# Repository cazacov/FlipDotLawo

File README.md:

# FlipDot34

Controller for the flip-dot display with 34-pin connector. For example produced by Lawo-Luminator-Europa Mark IV Industries GmbH.

Version 28x19

Version 28x24 with LED lights

## Connector Pinout
| Pin |  Function | Pin |  Function |
| --- | ------ | --- | ------ |
| 1   | GND  | 2   | GND  | 
| 3   | GND  | 4   | GND  | 
| 5   | 5V  |  6   | 5V  | 
| 7   | A0-X | 8 | DATA-X |
| 9   | A1-X | 10 | ENABLE-Y-SET |
| 11   | A2-X | 12 | ENABLE-Y-RESET |e
| 13   | B0-X | 14 | ENABLE-X-1 |
| 15   | B1-X | 16 | ENABLE-X-2 |
| 17   | A0-Y | 18 | ENABLE-X-3 |
| 19   | A1-Y | 20 | ENABLE-X-4 |
| 21   | A2-Y | 22 | ENABLE-X-5 |
| 23   | B0-Y | 24 | ENABLE-X-6 |
| 25   | B1-Y | 26 | ENABLE-X-7 |
| 27   | n/c | 28 | ENABLE-X-8 |
| 29   | 24V  |  30   | 24V  | 
| 31   | GND  | 32   | GND  | 
| 33   | GND  | 34   | GND  | 

## Chaining Multiple Displays in a Row

Driver board has two connectors. The output connector ST2 mostly duplicates 1:1 singnals from the input ST1 but ENABLE-X- signals are shifted. 

| Pin | INPUT  ST1 |  OUTPUT ST2 |
| --- | ---------- | ---------- |
| 13  | ENABLE-X-1 | ENABLE-X-2 |
| 15  | ENABLE-X-2 | ENABLE-X-3 |
| 17  | ENABLE-X-3 | ENABLE-X-4 |
| 19  | ENABLE-X-4 | ENABLE-X-5 |
| 21  | ENABLE-X-5 | ENABLE-X-6 |
| 23  | ENABLE-X-6 | ENABLE-X-7 |
| 25  | ENABLE-X-7 | ENABLE-X-8 |
| 17  | ENABLE-X-8 | ENABLE-X-1 |

The ENABLE input of FP2800 X Driver is always connected to ENABLE-X-1 connector pin. For example when ENABLE-X-3 is set to HIGH the first two displays in a row will ignore it, but after two decrements the signal will be applied to ENABLE-X-1 ST1 of the third display matrix and will activate it.

## Driver Boards

### Prototype

This prototype uses Arduino Nano and two 74HC595 shift registers to control up to 6 matrices. By adding another 595 it can control up to 8 display matrices.

### FlipDot34Nano

Driver board with Arduino Nano and three 74HC595 shift registers opitmized for single-sided PCB that can be milled with 3018 CNC. 3 digital pins are used for controlling shift registers, analog pins A4 and A5 can be used to receive commands over I2C. Pins A0-A2 connected to DIP switches choosing I2C address.

Schematic in KiCad 6 format checked in under .\Driver-boards\FlipDot34Nano\schematic\FlipDot34Nano

---
All trademarks, logos and brand names are the property of their respective owners. All company, product and service names are for identification purposes only. 

It's a hobby project; I am not affiliated with any  company producing flip-dot displays.

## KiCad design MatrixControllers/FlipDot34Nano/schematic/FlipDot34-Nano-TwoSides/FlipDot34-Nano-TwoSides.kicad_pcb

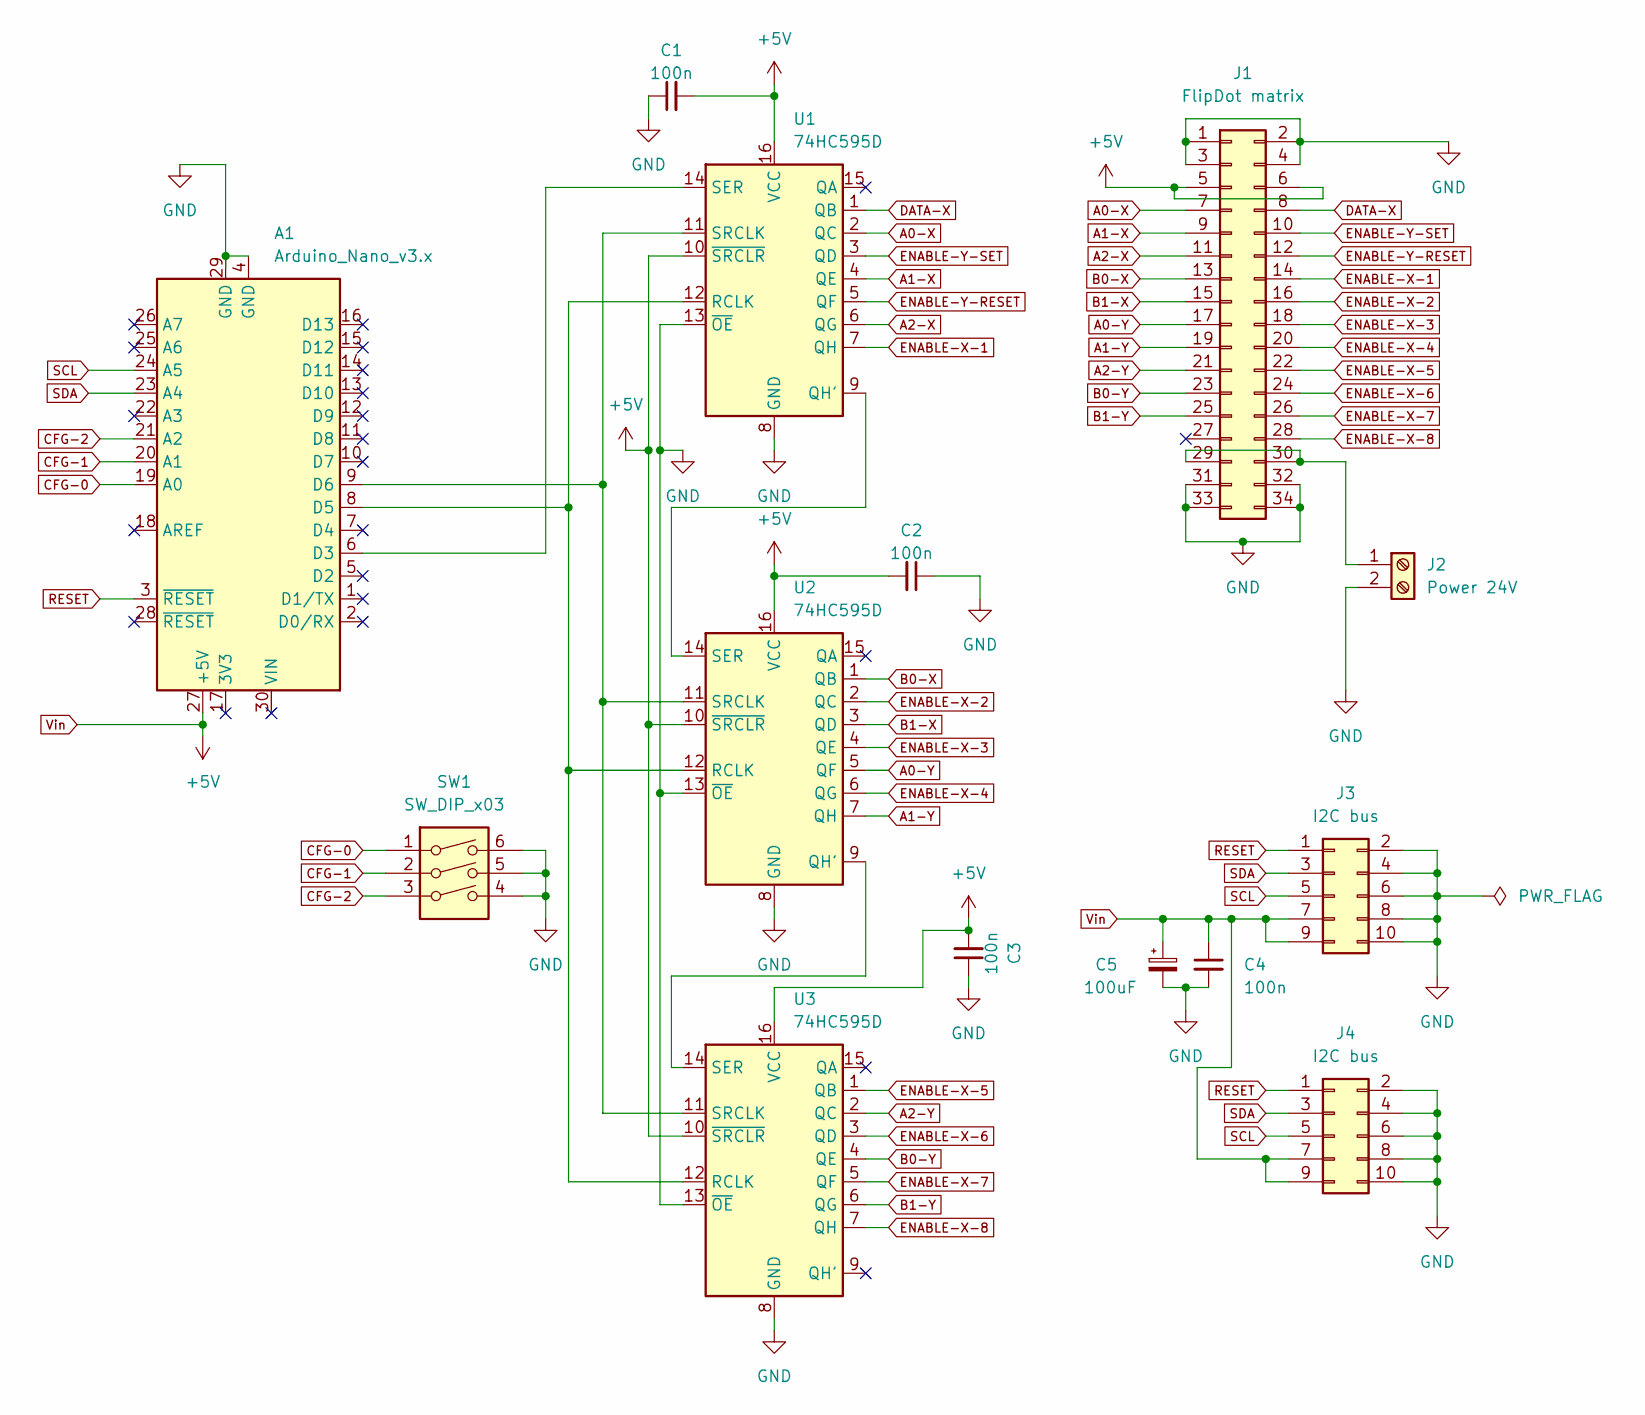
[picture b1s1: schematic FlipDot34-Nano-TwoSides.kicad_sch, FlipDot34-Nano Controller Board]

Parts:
A1: Arduino_Nano_v3.x; Arduino_Nano
C1, C2, C3, C4: 100n; C_1206_3216Metric_Pad1.33x1.80mm_HandSolder
C5: 100uF; CP_Radial_D8.0mm_P3.50mm
J1: FlipDot matrix; PinSocket_2x17_P2.54mm_Vertical
J2: Power 24V; TerminalBlock_bornier-2_P5.08mm
J3, J4: I2C bus; IDC-Header_2x05_P2.54mm_Vertical
SW1: SW_DIP_x03; SW_DIP_SPSTx03_Slide_9.78x9.8mm_W7.62mm_P2.54mm
U1, U2, U3: 74HC595D; SO-16_3.9x9.9mm_P1.27mm

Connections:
A0-X: J1.7, U1.2 (QC)
A0-Y: J1.17, U2.5 (QF)
A1-X: J1.9, U1.4 (QE)
A1-Y: J1.19, U2.7 (QH)
A2-X: J1.11, U1.6 (QG)
A2-Y: J1.21, U3.2 (QC)
B0-X: J1.13, U2.1 (QB)
B0-Y: J1.23, U3.4 (QE)
B1-X: J1.15, U2.3 (QD)
B1-Y: J1.25, U3.6 (QG)
CFG-0: A1.19 (A0), SW1.1
CFG-1: A1.20 (A1), SW1.2
CFG-2: A1.21 (A2), SW1.3
DATA-X: J1.8, U1.1 (QB)
ENABLE-X-1: J1.14, U1.7 (QH)
ENABLE-X-2: J1.16, U2.2 (QC)
ENABLE-X-3: J1.18, U2.4 (QE)
ENABLE-X-4: J1.20, U2.6 (QG)
ENABLE-X-5: J1.22, U3.1 (QB)
ENABLE-X-6: J1.24, U3.3 (QD)
ENABLE-X-7: J1.26, U3.5 (QF)
ENABLE-X-8: J1.28, U3.7 (QH)
ENABLE-Y-RESET: J1.12, U1.5 (QF)
ENABLE-Y-SET: J1.10, U1.3 (QD)
GND: A1.4 (GND), A1.29 (GND), C1.1, C2.1, C3.1, C4.2, C5.2, J1.1, J1.2, J1.3, J1.4, J1.31, J1.32, J1.33, J1.34, J2.2, J3.2, J3.4, J3.6, J3.8, J3.10, J4.2, J4.4, J4.6, J4.8, J4.10, SW1.4, SW1.5, SW1.6, U1.8 (GND), U1.13 (~OE), U2.8 (GND), U2.13 (~OE), U3.8 (GND), U3.13 (~OE)
unnamed: A1.6 (D3), U1.14 (SER)
unnamed: A1.8 (D5), U1.12 (RCLK), U2.12 (RCLK), U3.12 (RCLK)
unnamed: A1.9 (D6), U1.11 (SRCLK), U2.11 (SRCLK), U3.11 (SRCLK)
unnamed: J1.29, J1.30, J2.1
unnamed: U1.9 (QH'), U2.14 (SER)
unnamed: U2.9 (QH'), U3.14 (SER)
RESET: A1.3 (~RESET), J3.1, J4.1
SCL: A1.24 (A5), J3.5, J4.5
SDA: A1.23 (A4), J3.3, J4.3
Vin: A1.27 (+5V), C1.2, C2.2, C3.2, C4.1, C5.1, J1.5, J1.6, J3.7, J3.9, J4.7, J4.9, U1.10 (~SRCLR), U1.16 (VCC), U2.10 (~SRCLR), U2.16 (VCC), U3.10 (~SRCLR), U3.16 (VCC)

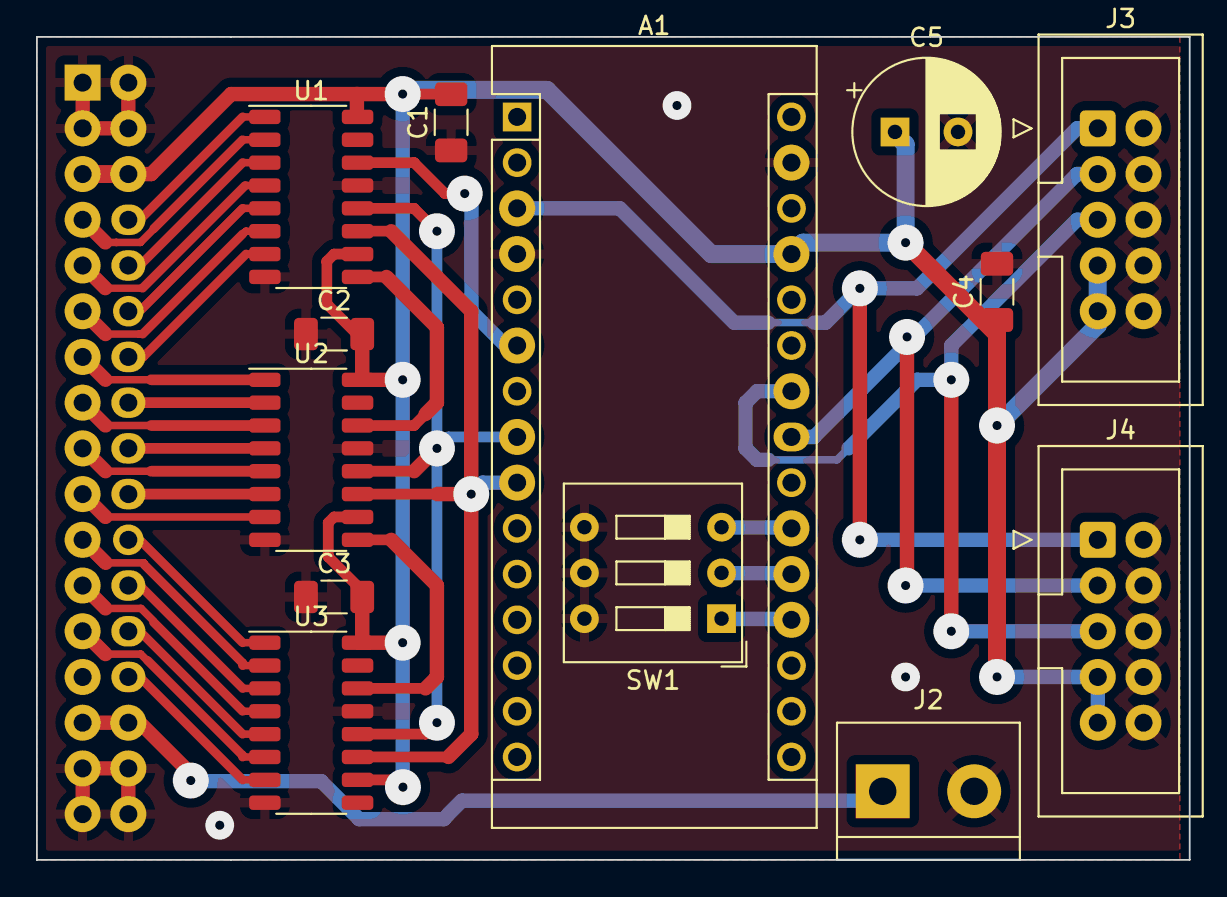
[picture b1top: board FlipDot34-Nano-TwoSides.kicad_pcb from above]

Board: 2 copper layers, 64.0 x 45.7 mm, 14 parts (1 on the bottom side), 35 nets.

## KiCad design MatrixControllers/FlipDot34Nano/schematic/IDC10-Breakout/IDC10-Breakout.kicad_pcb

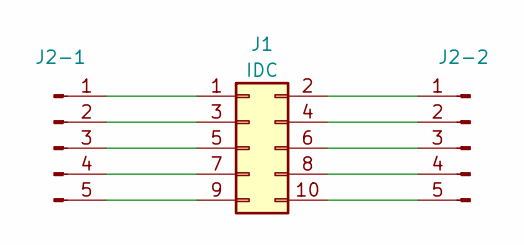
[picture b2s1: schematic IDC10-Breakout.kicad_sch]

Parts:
J1: IDC; IDC-Header_2x05_P2.54mm_Vertical
J2-1, J2-2: PinHeader_1x05_P2.54mm_Vertical

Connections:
unnamed: J1.1, J2-1.1
unnamed: J1.2, J2-2.1
unnamed: J1.3, J2-1.2
unnamed: J1.4, J2-2.2
unnamed: J1.5, J2-1.3
unnamed: J1.6, J2-2.3
unnamed: J1.7, J2-1.4
unnamed: J1.8, J2-2.4
unnamed: J1.9, J2-1.5
unnamed: J1.10, J2-2.5

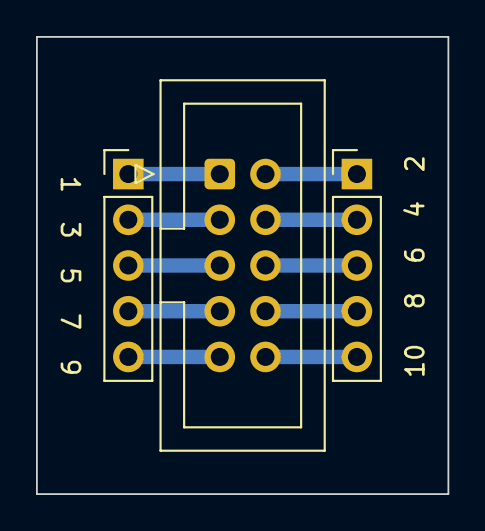
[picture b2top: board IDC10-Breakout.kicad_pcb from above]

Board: 2 copper layers, 22.9 x 25.4 mm, 3 parts (0 on the bottom side), 10 nets.

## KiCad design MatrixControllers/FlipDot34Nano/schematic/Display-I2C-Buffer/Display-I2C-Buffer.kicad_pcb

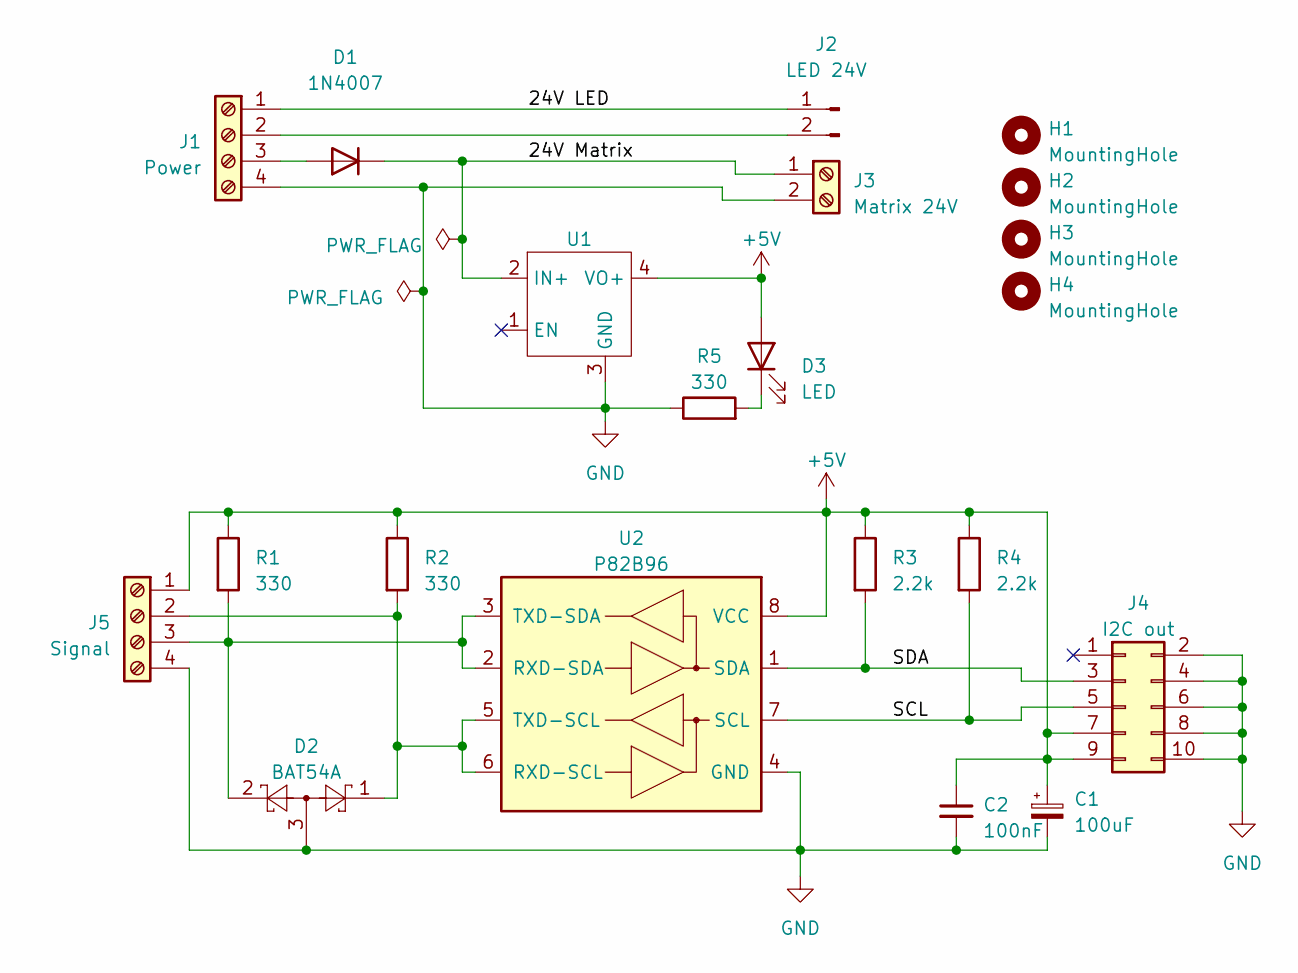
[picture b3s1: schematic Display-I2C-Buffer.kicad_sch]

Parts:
C1: 100uF; CP_Radial_D8.0mm_P3.50mm
C2: 100nF; C_1206_3216Metric
D1: 1N4007; D_DO-41_SOD81_P10.16mm_Horizontal
D2: BAT54A; SOT-23
D3: LED; LED_0805_2012Metric
H1, H2, H3, H4: MountingHole; MountingHole_3.2mm_M3_DIN965
J1: Power; TerminalBlock_bornier-4_P5.08mm
J2: LED 24V; Molex_KK-396_A-41791-0002_1x02_P3.96mm_Vertical
J3: Matrix 24V; TerminalBlock_bornier-2_P5.08mm
J4: I2C out; IDC-Header_2x05_P2.54mm_Vertical
J5: Signal; JST_EH_B4B-EH-A_1x04_P2.50mm_Vertical
R1, R2, R5: 330; R_1206_3216Metric
R3, R4: 2.2k; R_1206_3216Metric
U1: Mini DC-DC
U2: P82B96; SOIC-8_3.9x4.9mm_P1.27mm

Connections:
+5V: C1.1, C2.1, D3.2 (A), J4.7, J4.9, J5.1, R1.1, R2.1, R3.1, R4.1, U1.4 (VO+), U2.8 (VCC)
/24V LED: J1.1, J2.1
/24V Matrix: D1.1 (K), J3.1, U1.2 (IN+)
/SCL: J4.5, R4.2, U2.7 (SCL)
/SDA: J4.3, R3.2, U2.1 (SDA)
GND: C1.2, C2.2, D2.3, J1.4, J3.2, J4.2, J4.4, J4.6, J4.8, J4.10, J5.4, R5.1, U1.3 (GND), U2.4 (GND)
unnamed: D1.2 (A), J1.3
unnamed: D3.1 (K), R5.2
unnamed: J1.2, J2.2
unnamed: D2.1, J5.2, R2.2, U2.5 (TXD-SCL), U2.6 (RXD-SCL)
unnamed: D2.2, J5.3, R1.2, U2.2 (RXD-SDA), U2.3 (TXD-SDA)

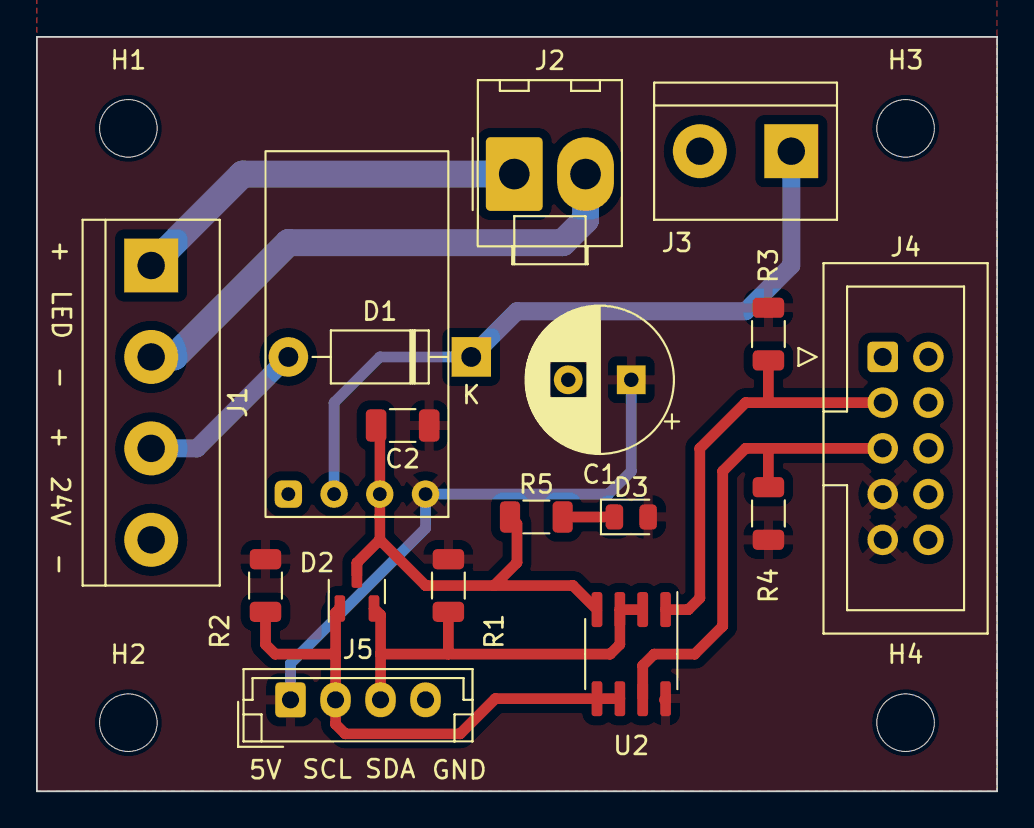
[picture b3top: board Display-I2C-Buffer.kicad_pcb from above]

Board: 2 copper layers, 53.3 x 41.9 mm, 21 parts (0 on the bottom side), 11 nets.

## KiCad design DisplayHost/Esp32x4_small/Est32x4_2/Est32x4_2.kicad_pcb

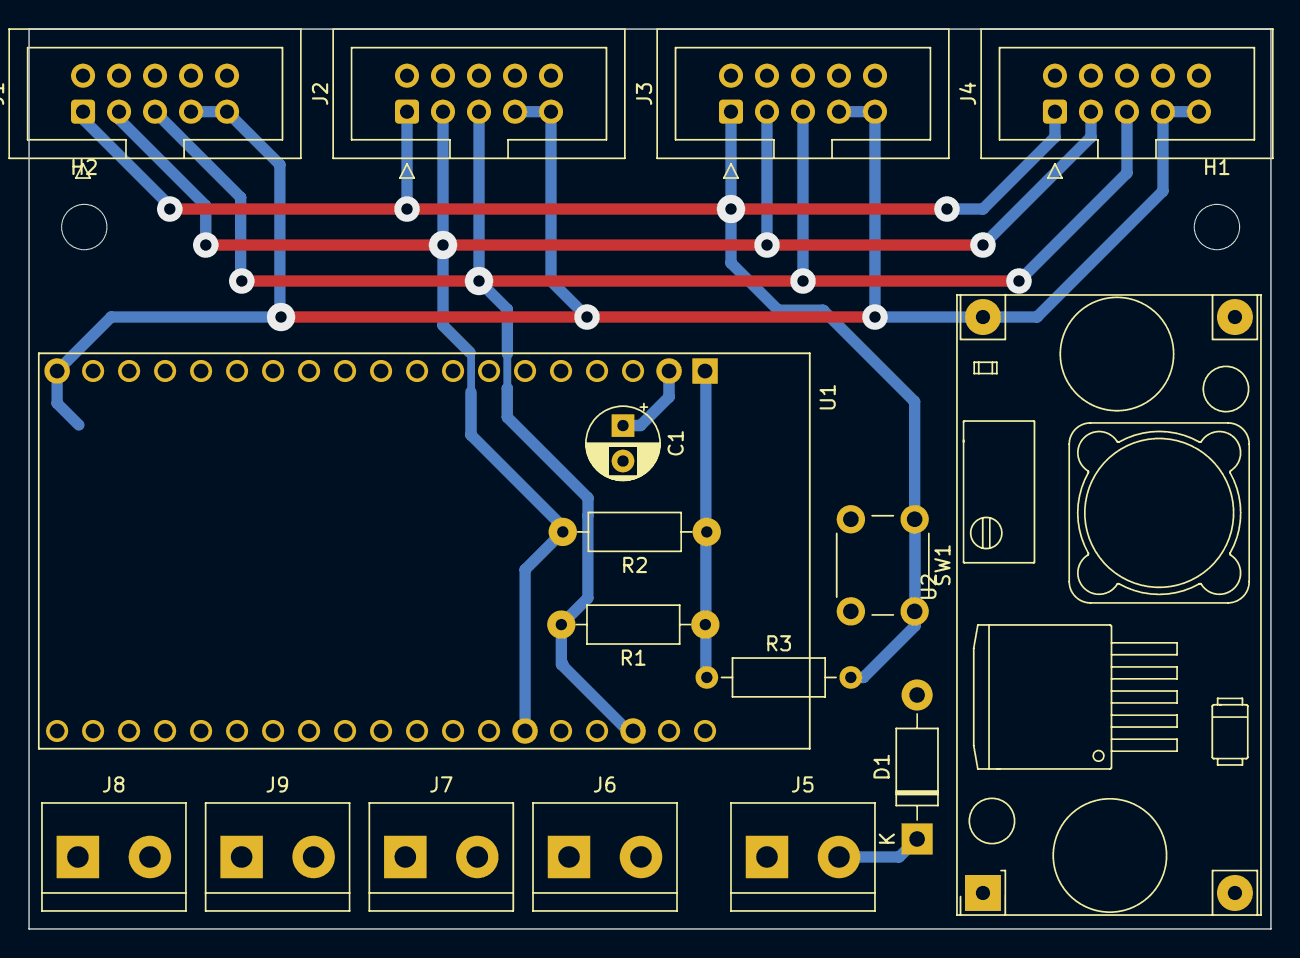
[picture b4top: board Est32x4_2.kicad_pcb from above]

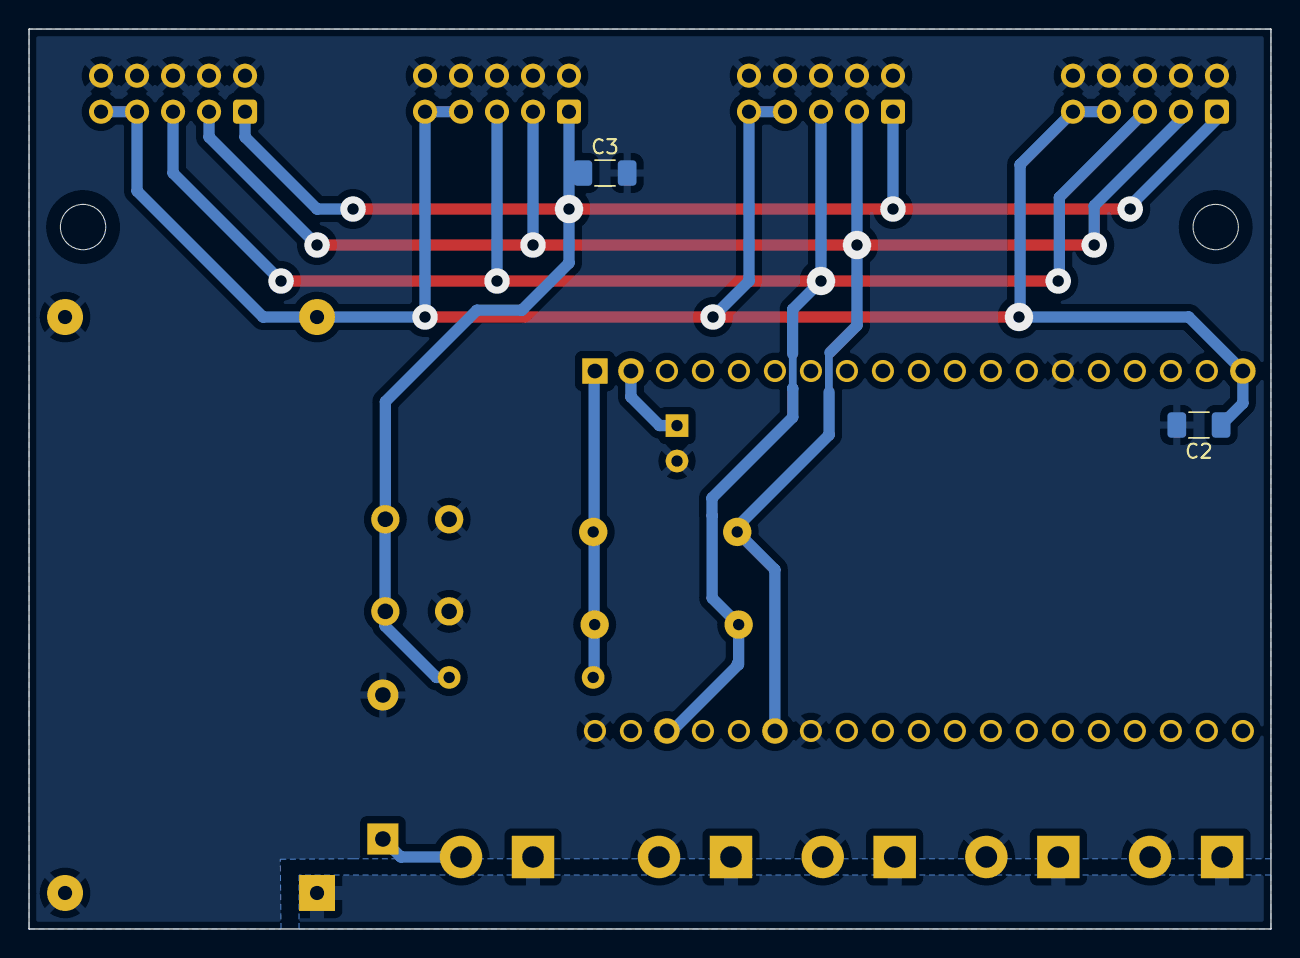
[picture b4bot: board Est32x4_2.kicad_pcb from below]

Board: 2 copper layers, 87.6 x 63.5 mm, 21 parts (2 on the bottom side), 9 nets.

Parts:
C1: 10uF; CP_Radial_D5.0mm_P2.50mm
C2, C3: 100n; C_1206_3216Metric_Pad1.33x1.80mm_HandSolder
D1: 1N5819; D_DO-41_SOD81_P10.16mm_Horizontal
H1, H2: MountingHole; MountingHole_3.2mm_M3
J1, J2, J3, J4: I2C bus; IDC-Header_2x05_P2.54mm_Vertical
J5: 24V In; TerminalBlock_bornier-2_P5.08mm
J6, J7, J8, J9: 24V Out; TerminalBlock_bornier-2_P5.08mm
R1, R2, R3: 10k; R_Axial_DIN0207_L6.3mm_D2.5mm_P10.16mm_Horizontal
SW1: SW_Push_Dual; SW_PUSH_6mm_H5mm
U1: ESP32-DEVKITC-32D; MODULE_ESP32-DEVKITC-32D
U2: DC-DC StepDown 5V; DCDC_StepDown_LM2596

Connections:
GND: C1.2, C2.2, C3.2, D1.2 (A), J1.2, J1.4, J1.6, J1.8, J1.10, J2.2, J2.4, J2.6, J2.8, J2.10, J3.2, J3.4, J3.6, J3.8, J3.10, J4.2, J4.4, J4.6, J4.8, J4.10, J6.2, J7.2, J8.2, J9.2, SW1.2, U1.14 (GND1), U1.20 (GND3), U1.26 (GND2), U2.2 (GND), U2.3 (GND)
unnamed: C1.1, U1.2 (EN)
unnamed: D1.1 (K), J5.2
RESET: C3.1, J1.1, J2.1, J3.1, J4.1, R3.2, SW1.1
SCL: J1.5, J2.5, J3.5, J4.5, R1.2, U1.22 (IO22)
SDA: J1.3, J2.3, J3.3, J4.3, R2.2, U1.25 (IO21)
VCC: R1.1, R2.1, R3.1, U1.1 (3V3)
VOut: C2.1, J1.7, J1.9, J2.7, J2.9, J3.7, J3.9, J4.7, J4.9, U1.19 (EXT_5V), U2.4 (Vout)
Vin: J5.1, J6.1, J7.1, J8.1, J9.1, U2.1 (Vin)

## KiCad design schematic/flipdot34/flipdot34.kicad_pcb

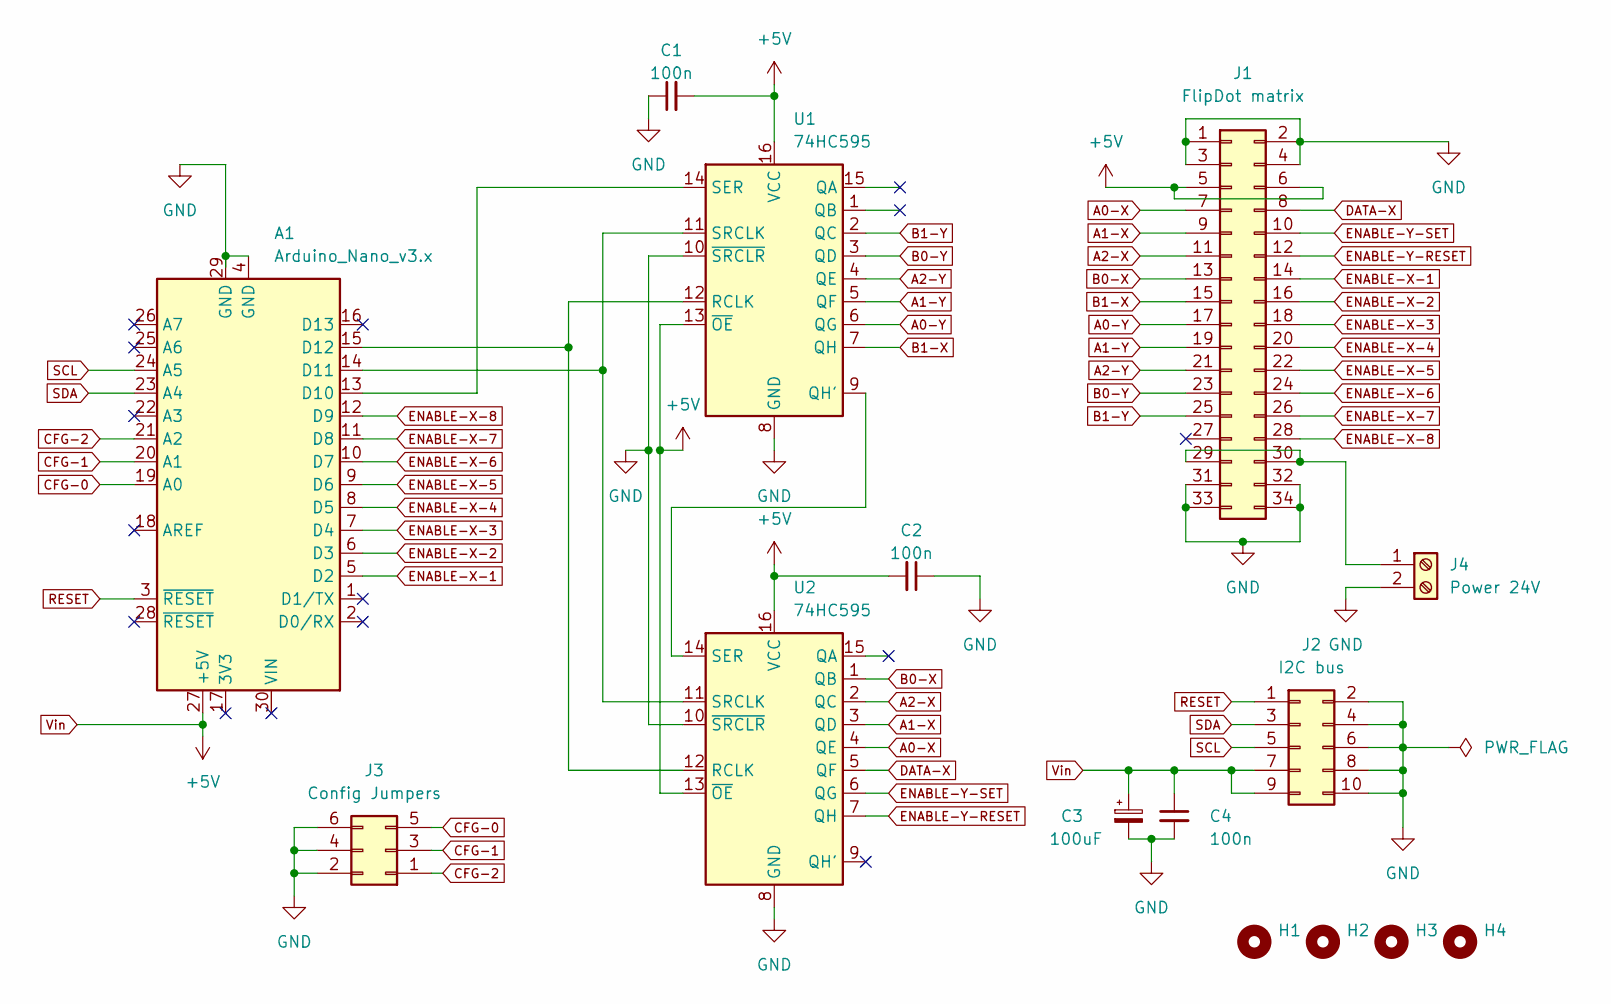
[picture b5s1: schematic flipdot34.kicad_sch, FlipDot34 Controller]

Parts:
A1: Arduino_Nano_v3.x; Arduino_Nano
C1, C2, C4: 100n; C_Disc_D5.0mm_W2.5mm_P5.00mm
C3: 100uF; CP_Radial_D6.3mm_P2.50mm
H1, H2, H3, H4: MountingHole; MountingHole_3.2mm_M3
J1: FlipDot matrix; IDC-Header_2x17_P2.54mm_Vertical
J2: I2C bus; IDC-Header_2x05_P2.54mm_Vertical
J3: Config Jumpers; PinHeader_2x03_P2.54mm_Vertical
J4: Power 24V; TerminalBlock_bornier-2_P5.08mm
U1, U2: 74HC595; DIP-16_W7.62mm_LongPads

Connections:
A0-X: J1.7, U2.4 (QE)
A0-Y: J1.17, U1.6 (QG)
A1-X: J1.9, U2.3 (QD)
A1-Y: J1.19, U1.5 (QF)
A2-X: J1.11, U2.2 (QC)
A2-Y: J1.21, U1.4 (QE)
B0-X: J1.13, U2.1 (QB)
B0-Y: J1.23, U1.3 (QD)
B1-X: J1.15, U1.7 (QH)
B1-Y: J1.25, U1.2 (QC)
CFG-0: A1.19 (A0), J3.5
CFG-1: A1.20 (A1), J3.3
CFG-2: A1.21 (A2), J3.1
DATA-X: J1.8, U2.5 (QF)
ENABLE-X-1: A1.5 (D2), J1.14
ENABLE-X-2: A1.6 (D3), J1.16
ENABLE-X-3: A1.7 (D4), J1.18
ENABLE-X-4: A1.8 (D5), J1.20
ENABLE-X-5: A1.9 (D6), J1.22
ENABLE-X-6: A1.10 (D7), J1.24
ENABLE-X-7: A1.11 (D8), J1.26
ENABLE-X-8: A1.12 (D9), J1.28
ENABLE-Y-RESET: J1.12, U2.7 (QH)
ENABLE-Y-SET: J1.10, U2.6 (QG)
GND: A1.4 (GND), A1.29 (GND), C1.1, C2.1, C3.2, C4.2, J1.1, J1.2, J1.3, J1.4, J1.31, J1.32, J1.33, J1.34, J2.2, J2.4, J2.6, J2.8, J2.10, J3.2, J3.4, J3.6, J4.2, U1.8 (GND), U1.10 (~SRCLR), U2.8 (GND), U2.10 (~SRCLR)
unnamed: A1.13 (D10), U1.14 (SER)
unnamed: A1.14 (D11), U1.11 (SRCLK), U2.11 (SRCLK)
unnamed: A1.15 (D12), U1.12 (RCLK), U2.12 (RCLK)
unnamed: J1.29, J1.30, J4.1
unnamed: U1.9 (QH'), U2.14 (SER)
RESET: A1.3 (~RESET), J2.1
SCL: A1.24 (A5), J2.5
SDA: A1.23 (A4), J2.3
Vin: A1.27 (+5V), C1.2, C2.2, C3.1, C4.1, J1.5, J1.6, J2.7, J2.9, U1.13 (~OE), U1.16 (VCC), U2.13 (~OE), U2.16 (VCC)

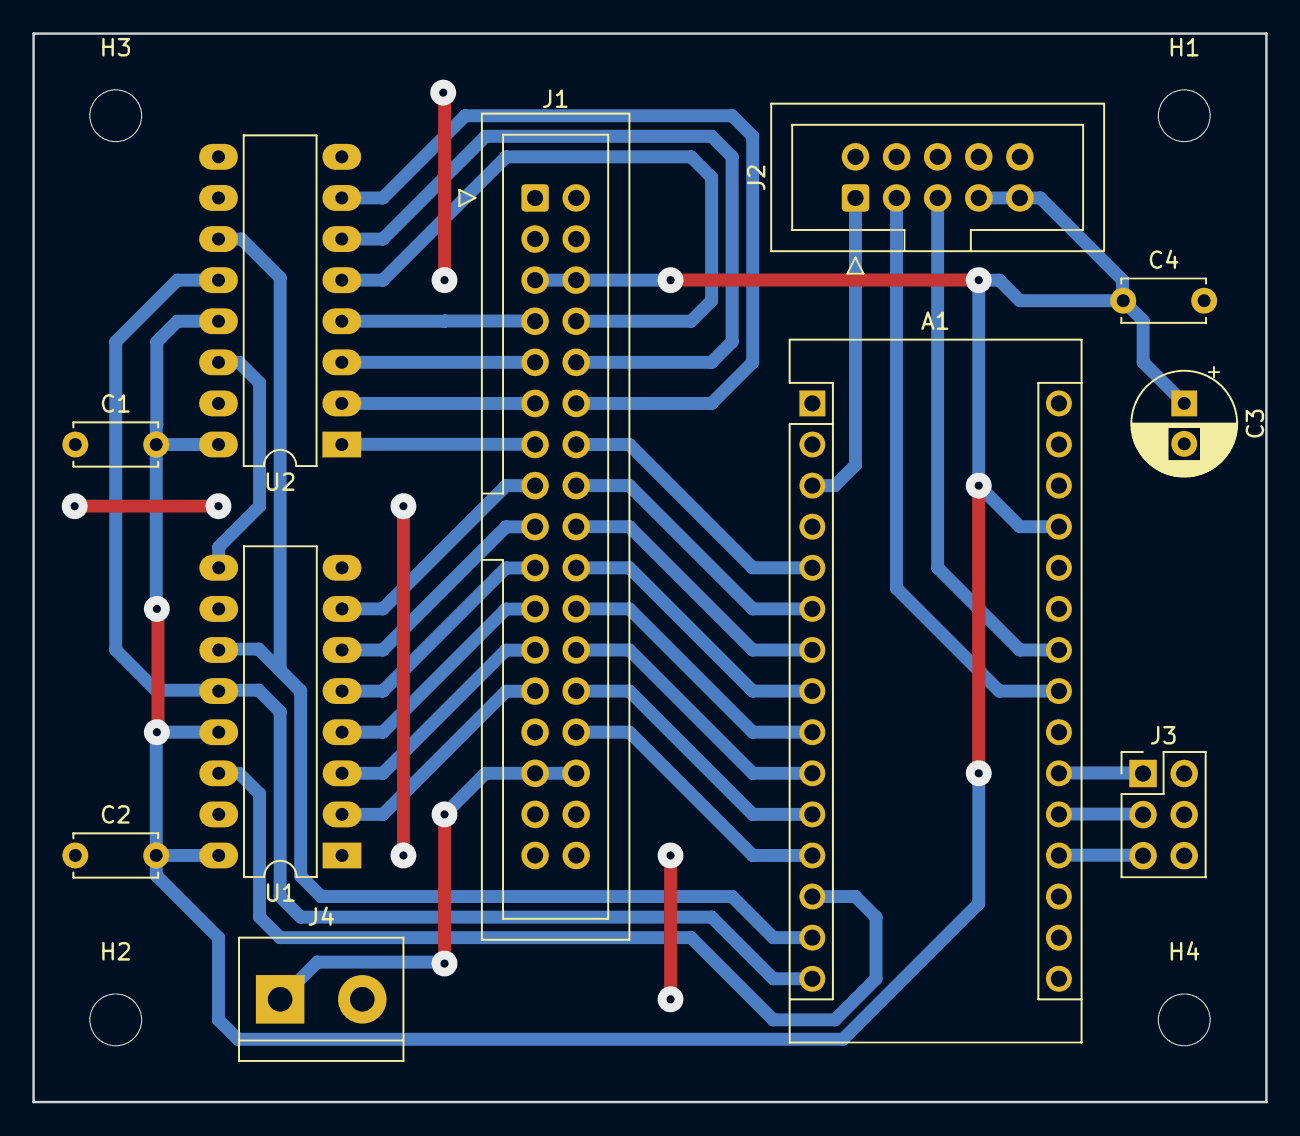
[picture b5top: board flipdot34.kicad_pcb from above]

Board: 2 copper layers, 76.2 x 66.0 mm, 15 parts (0 on the bottom side), 34 nets.

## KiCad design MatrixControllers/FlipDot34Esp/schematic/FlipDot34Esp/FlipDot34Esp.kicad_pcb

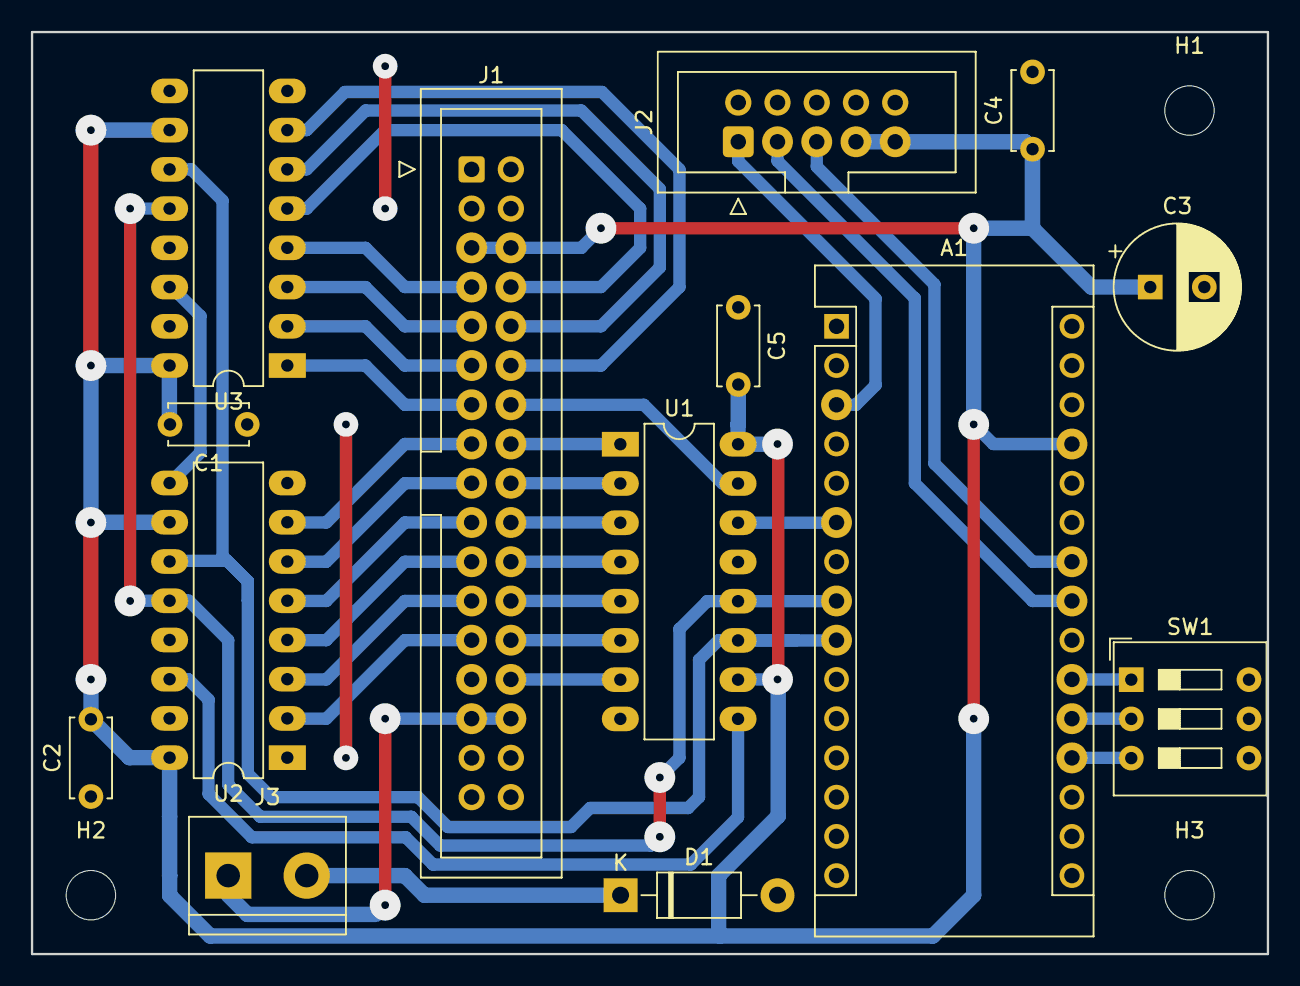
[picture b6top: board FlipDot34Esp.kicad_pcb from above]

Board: 2 copper layers, 80.0 x 59.7 mm, 17 parts (0 on the bottom side), 36 nets.

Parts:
A1: Arduino_Nano_v3.x; Arduino_Nano
C1, C2, C4, C5: 100n; C_Disc_D5.0mm_W2.5mm_P5.00mm
C3: 100uF; CP_Radial_D8.0mm_P3.50mm
D1: 1N5819; D_DO-41_SOD81_P10.16mm_Horizontal
H1, H2, H3: MountingHole; MountingHole_3.2mm_M3
J1: FlipDot matrix; IDC-Header_2x17_P2.54mm_Vertical
J2: I2C bus; IDC-Header_2x05_P2.54mm_Vertical
J3: Power 24V; TerminalBlock_bornier-2_P5.08mm
SW1: SW_DIP_x03; SW_DIP_SPSTx03_Slide_9.78x9.8mm_W7.62mm_P2.54mm
U1, U2, U3: 74HC595; DIP-16_W7.62mm_LongPads

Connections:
A0-X: J1.7, U3.4 (QE)
A0-Y: J1.17, U2.6 (QG)
A1-X: J1.9, U3.3 (QD)
A1-Y: J1.19, U2.5 (QF)
A2-X: J1.11, U3.2 (QC)
A2-Y: J1.21, U2.4 (QE)
B0-X: J1.13, U3.1 (QB)
B0-Y: J1.23, U2.3 (QD)
B1-X: J1.15, U2.7 (QH)
B1-Y: J1.25, U2.2 (QC)
CFG-0: A1.19 (A0), SW1.3
CFG-1: A1.20 (A1), SW1.2
CFG-2: A1.21 (A2), SW1.1
DATA-X: J1.8, U3.5 (QF)
ENABLE-X-1: J1.14, U1.15 (QA)
ENABLE-X-2: J1.16, U1.1 (QB)
ENABLE-X-3: J1.18, U1.2 (QC)
ENABLE-X-4: J1.20, U1.3 (QD)
ENABLE-X-5: J1.22, U1.4 (QE)
ENABLE-X-6: J1.24, U1.5 (QF)
ENABLE-X-7: J1.26, U1.6 (QG)
ENABLE-X-8: J1.28, U1.7 (QH)
ENABLE-Y-RESET: J1.12, U3.7 (QH)
ENABLE-Y-SET: J1.10, U3.6 (QG)
GND: A1.4 (GND), A1.29 (GND), C1.1, C2.1, C3.2, C4.2, C5.1, D1.2 (A), J1.1, J1.2, J1.3, J1.4, J1.31, J1.32, J1.33, J1.34, J2.2, J2.4, J2.6, J2.8, J2.10, SW1.4, SW1.5, SW1.6, U1.8 (GND), U1.13 (~OE), U2.8 (GND), U2.13 (~OE), U3.8 (GND), U3.13 (~OE)
unnamed: A1.6 (D3), U1.14 (SER)
unnamed: A1.8 (D5), U1.12 (RCLK), U2.12 (RCLK), U3.12 (RCLK)
unnamed: A1.9 (D6), U1.11 (SRCLK), U2.11 (SRCLK), U3.11 (SRCLK)
unnamed: D1.1 (K), J3.2
unnamed: J1.29, J1.30, J3.1
unnamed: U1.9 (QH'), U2.14 (SER)
unnamed: U2.9 (QH'), U3.14 (SER)
RESET: A1.3 (~RESET), J2.1
SCL: A1.24 (A5), J2.5
SDA: A1.23 (A4), J2.3
Vin: A1.27 (+5V), C1.2, C2.2, C3.1, C4.1, C5.2, J1.5, J1.6, J2.7, J2.9, U1.10 (~SRCLR), U1.16 (VCC), U2.10 (~SRCLR), U2.16 (VCC), U3.10 (~SRCLR), U3.16 (VCC)

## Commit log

2022-03-27 Driver for Lawo flip-dot displays
2022-04-03 Support up to 6 matrices in a row
2022-04-04 Refactoring
2022-04-06 Support AdafruitGFX
2022-04-06 Improve performance with frame buffer
2022-04-08 README
2022-04-09 Document chaining of displays
2022-04-09 Code examples
2022-04-11 Add controller schematic
2022-04-12 Schematic - add communication and config connectors
2022-04-13 Add +24V terminal
2022-04-13 Assign footprints
2022-04-14 Add board dimensions
2022-04-14 Add mounting holes
2022-04-15 DRC tests pass
2022-04-15 Minor fixes
2022-05-01 Add FlipDot34Esp board
2022-05-04 Design 2-sided PCB
2022-05-05 Add ground polygon
2022-05-15 Create MatrixControllerI2C example
2022-05-15 Fix bugs
2022-05-15 Add command processor
2022-05-15 Add more commands
2022-05-15 Add Bitmap command
2022-05-16 Windows display host (BusPirate)
2022-05-18 Send bitmaps over I2c
2022-05-18 Fix memory leaks
2022-05-27 Refactoring: inverse bits order
2022-05-28 Improved command processor
2022-09-17 Add second I2C interface header
2022-09-18 Add SetDelays command
2022-09-18 Version 3 of the matrix controller board
2022-09-25 Bad Apple demo
2023-02-18 Matrix 28x24
